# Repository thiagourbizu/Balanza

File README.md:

Balanza para Self-Checkout Girboy

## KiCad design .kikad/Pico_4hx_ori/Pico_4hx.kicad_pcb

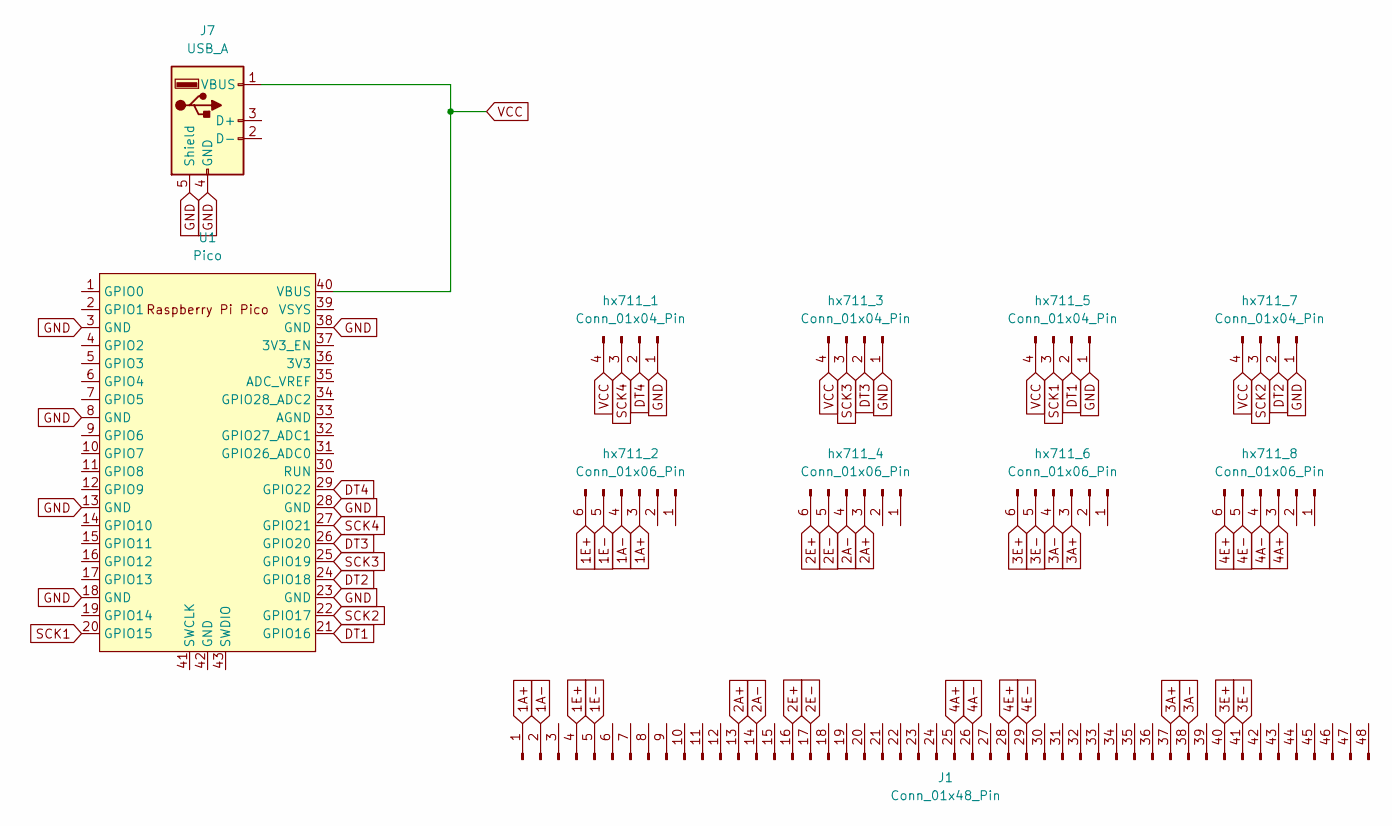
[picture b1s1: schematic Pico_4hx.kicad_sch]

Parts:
J1: Conn_01x48_Pin; RJ45_Amphenol_RJHSE538X-04
J7: USB_A; USB_A_Molex_67643_Horizontal
U1: Pico; RPi_Pico_SMD_TH
hx711_1, hx711_3, hx711_5, hx711_7: Conn_01x04_Pin; PinSocket_1x04_P2.54mm_Vertical
hx711_2, hx711_4, hx711_6, hx711_8: Conn_01x06_Pin; PinSocket_1x06_P2.54mm_Vertical

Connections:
1A+: J1.1, hx711_2.3
1A-: J1.2, hx711_2.4
1E+: J1.4, hx711_2.6
1E-: J1.5, hx711_2.5
2A+: J1.13, hx711_4.3
2A-: J1.14, hx711_4.4
2E+: J1.16, hx711_4.6
2E-: J1.17, hx711_4.5
3A+: J1.37, hx711_6.3
3A-: J1.38, hx711_6.4
3E+: J1.40, hx711_6.6
3E-: J1.41, hx711_6.5
4A+: J1.25, hx711_8.3
4A-: J1.26, hx711_8.4
4E+: J1.28, hx711_8.6
4E-: J1.29, hx711_8.5
DT1: U1.21 (GPIO16), hx711_5.2
DT2: U1.24 (GPIO18), hx711_7.2
DT3: U1.26 (GPIO20), hx711_3.2
DT4: U1.29 (GPIO22), hx711_1.2
GND: J7.4 (GND), J7.5 (Shield), U1.3 (GND), U1.8 (GND), U1.13 (GND), U1.18 (GND), U1.23 (GND), U1.28 (GND), U1.38 (GND), hx711_1.1, hx711_3.1, hx711_5.1, hx711_7.1
SCK1: U1.20 (GPIO15), hx711_5.3
SCK2: U1.22 (GPIO17), hx711_7.3
SCK3: U1.25 (GPIO19), hx711_3.3
SCK4: U1.27 (GPIO21), hx711_1.3
VCC: J7.1 (VBUS), U1.40 (VBUS), hx711_1.4, hx711_3.4, hx711_5.4, hx711_7.4

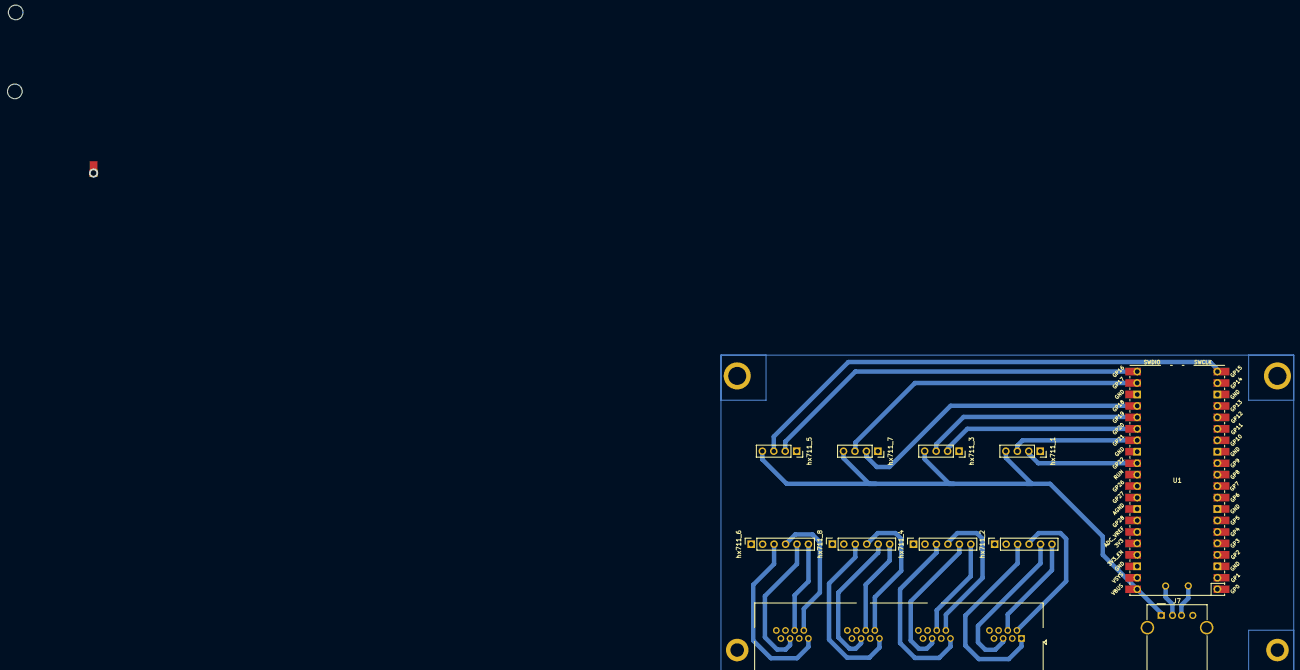
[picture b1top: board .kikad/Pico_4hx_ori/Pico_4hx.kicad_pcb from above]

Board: 2 copper layers, 11 parts (0 on the bottom side), 26 nets.

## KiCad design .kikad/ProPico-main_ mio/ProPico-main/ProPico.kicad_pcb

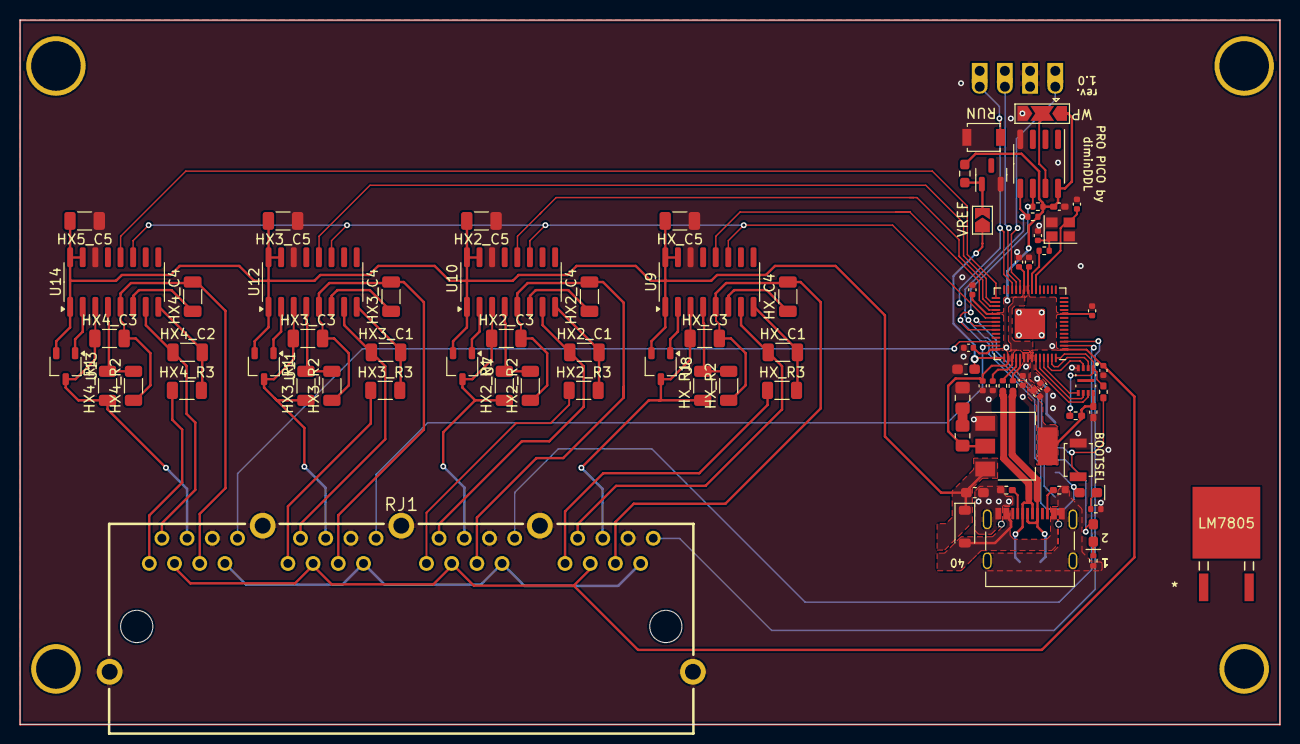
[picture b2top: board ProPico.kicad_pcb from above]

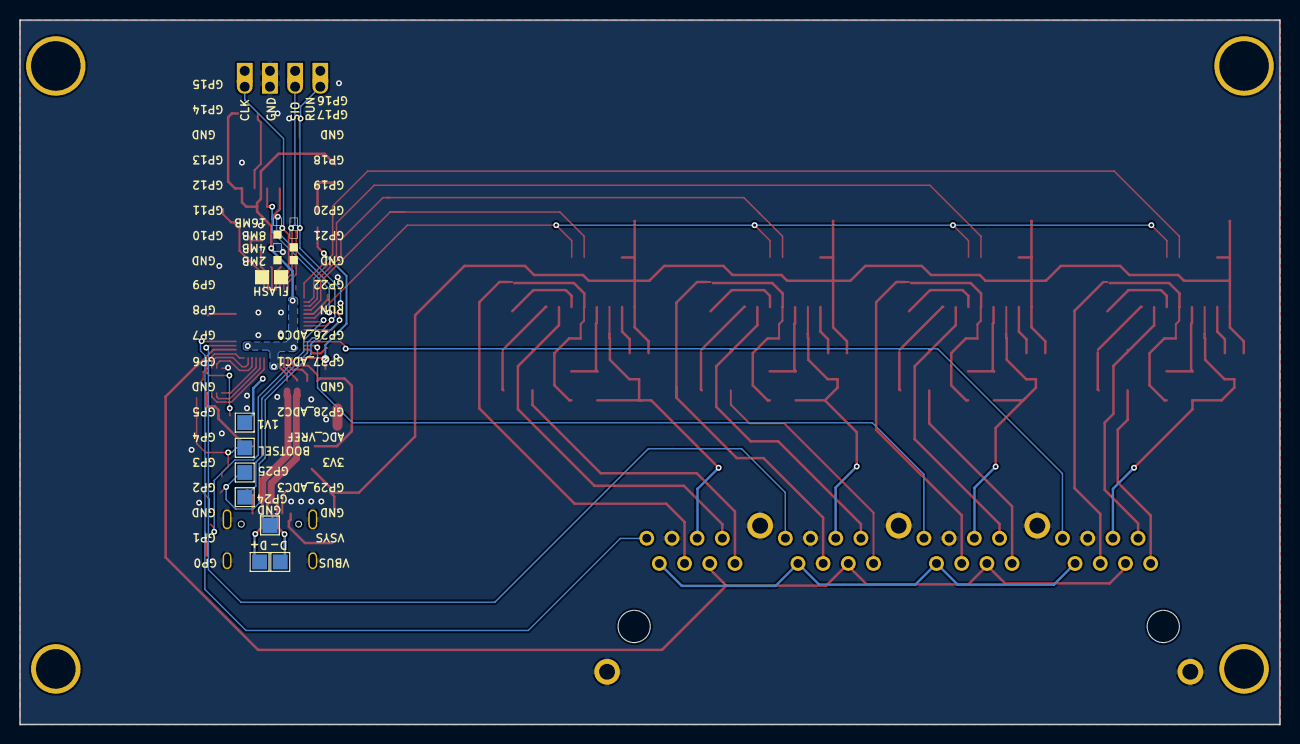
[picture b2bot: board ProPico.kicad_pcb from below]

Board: 2 copper layers, 127.0 x 71.0 mm, 91 parts (7 on the bottom side), 75 nets.

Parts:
C1, C5: 100n; C_0402_1005Metric_Pad0.74x0.62mm_HandSolder
C2, C3: 18p; C_0402_1005Metric
C4: 2.2u; C_0603_1608Metric_Pad1.08x0.95mm_HandSolder
C6: 10u; C_0805_2012Metric_Pad1.18x1.45mm_HandSolder
C7: 10n C0G; C_0603_1608Metric_Pad1.08x0.95mm_HandSolder
C8, C9, C11, C13, C14, C15, C16, C17, C18: 100n; C_0402_1005Metric
C10, C12: 1u; C_0402_1005Metric
D1: B5819W; D_SOD-123
D2, D3: LED; LED_0603_1608Metric_Pad1.05x0.95mm_HandSolder
HX2_C1, HX2_C3, HX3_C1, HX3_C3, HX4_C2, HX4_C3: 0.1uF; C_1206_3216Metric
HX2_C4, HX2_C5, HX3_C4, HX3_C5, HX4_C4, HX5_C5: 10uF; C_1206_3216Metric
HX2_R1, HX3_R1, HX4_R1: 20k; R_1206_3216Metric
HX2_R2, HX3_R2, HX4_R2: 8.2k; R_1206_3216Metric
HX2_R3, HX3_R3, HX4_R3: 1k; R_1206_3216Metric
HX_C1, HX_C3: 0.1uF; C_1206_3216Metric
HX_C4, HX_C5: 10uF; C_1206_3216Metric
HX_R1: 20k; R_1206_3216Metric
HX_R2: 8.2k; R_1206_3216Metric
HX_R3: 1k; R_1206_3216Metric
J1: USB_C_Receptacle_USB2.0; USB_C_Receptacle_Palconn_UTC16-G
J2: SWD; Pico_4pin
JP1: EEPROM_WP; SolderJumper-3_P2.0mm_Open_TrianglePad1.0x1.5mm
JP2: VREF; SolderJumper-2_P1.3mm_Open_TrianglePad1.0x1.5mm
LM7805: MC7805CDTRKG; DPAK-3_ONS-M
R1: 1k; R_0402_1005Metric_Pad0.72x0.64mm_HandSolder
R2: DNP; R_0402_1005Metric_Pad0.72x0.64mm_HandSolder
R3, R4: 5.1k; R_0402_1005Metric_Pad0.72x0.64mm_HandSolder
R5, R10, R11, R12, R13: 1k; R_0402_1005Metric
R6: 470mOhm; R_0805_2012Metric_Pad1.20x1.40mm_HandSolder
R7: 150; R_0603_1608Metric_Pad0.98x0.95mm_HandSolder
R8, R9: 27; R_0402_1005Metric
RJ1: DS1129-02-S80BP
SW1: BOOTSEL; SW_SPST_B3U-1000P
SW2: RES; SW_SPST_B3U-1000P
TP1: BOOTSEL; TestPoint_Pad_1.5x1.5mm
TP2: VREG; TestPoint_Pad_1.5x1.5mm
TP3: GP25; TestPoint_Pad_1.5x1.5mm
TP4: GND; TestPoint_Pad_1.5x1.5mm
TP5: D+; TestPoint_Pad_1.5x1.5mm
TP6: GP24; TestPoint_Pad_1.5x1.5mm
TP7: D-; TestPoint_Pad_1.5x1.5mm
U1: FM24CL16B; SOIC-8_3.9x4.9mm_P1.27mm
U2: W25Q16JVUXIQ; IC_W25Q16JVUXIQ_TR
U3: AMS1117-3.3; SOT-223-3_TabPin2
U4: LM4040DBZ-3; SOT-23
U5: RP2040; RP2040-QFN-56
U7, U8, U11, U13: MMBT5550LT1G; TSOT-23
U9, U10, U12, U14: HX711; SOP-16_3.9x9.9mm_P1.27mm
Y1: ECS-120-12-36-AGN-TR3; Crystal_SMD_2520-4Pin_2.5x2.0mm

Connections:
1A+: HX_R3.1, RJ1.41 (D1)
1A-: HX_C1.1, RJ1.42 (D2), U9.7 (INA-)
1E+: HX_C3.1, HX_R1.1, RJ1.44 (D4), U8.3 (COLLECTOR), U9.3 (AVDD)
1E-: HX_C3.2, HX_C4.2, HX_R2.1, RJ1.45 (D5), U9.5 (AGND)
2A+: HX2_R3.1, RJ1.31 (C1)
2A-: HX2_C1.1, RJ1.32 (C2), U10.7 (INA-)
2E+: HX2_C3.1, HX2_R1.1, RJ1.34 (C4), U7.3 (COLLECTOR), U10.3 (AVDD)
2E-: HX2_C3.2, HX2_C4.2, HX2_R2.1, RJ1.35 (C5), U10.5 (AGND)
3.3V: C1.1, C5.1, C11.1, C12.1, C13.1, C14.1, C15.1, C16.1, C17.1, C18.1, JP1.1 (A), R2.1, R6.2, R7.2, R10.1, R11.1, RJ1.13 (A3), RJ1.23 (B3), RJ1.33 (C3), RJ1.43 (D3), U1.8 (VDD), U2.8 (VCC), U3.2 (VO), U5.1 (IOVDD), U5.10 (IOVDD), U5.22 (IOVDD), U5.33 (IOVDD), U5.42 (IOVDD), U5.44 (VREG_IN), U5.48 (USB_VDD), U5.49 (IOVDD)
3A+: HX3_R3.1, RJ1.21 (B1)
3A-: HX3_C1.1, RJ1.22 (B2), U12.7 (INA-)
3E+: HX3_C3.1, HX3_R1.1, RJ1.24 (B4), U11.3 (COLLECTOR), U12.3 (AVDD)
3E-: HX3_C3.2, HX3_C4.2, HX3_R2.1, RJ1.25 (B5), U12.5 (AGND)
4A+: HX4_R3.1, RJ1.11 (A1)
4A-: HX4_C2.1, RJ1.12 (A2), U14.7 (INA-)
4E+: HX4_C3.1, HX4_R1.1, RJ1.14 (A4), U13.3 (COLLECTOR), U14.3 (AVDD)
4E-: HX4_C3.2, HX4_C4.2, HX4_R2.1, RJ1.15 (A5), U14.5 (AGND)
+1V1: C8.1, C9.1, C10.1, TP2.1, U5.23 (DVDD), U5.45 (VREG_VOUT), U5.50 (DVDD)
/3V0_VREF: JP2.2 (B), R7.1, U4.1 (K)
/ADC_VREF: C7.1, JP2.1 (A), U5.43 (ADC_AVDD)
/D+: J1.A6 (D+), J1.B6 (D+), R8.1, TP5.1
/D-: J1.A7 (D-), J1.B7 (D-), R9.1, TP7.1
/DN: R9.2, U5.46 (USB_DM)
/DP: R8.2, U5.47 (USB_DP)
/EEPROM_SCL: D3.2 (A), R11.2, TP3.1, U1.6 (SCL), U5.37 (GPIO25)
/EEPROM_SDA: R10.2, TP6.1, U1.5 (SDA), U5.36 (GPIO24)
/EEPROM_WP: JP1.2 (C), U1.7 (WP)
/GPIO23: D2.2 (A), U5.35 (GPIO23)
/QSPI_SCLK: U2.6 (CLK), U5.52 (QSPI_SCLK)
/QSPI_SD0: U2.5 (DI(IO0)), U5.53 (QSPI_SD0)
/QSPI_SD1: U2.2 (DO(IO1)), U5.55 (QSPI_SD1)
/QSPI_SD2: U2.3 (IO2), U5.54 (QSPI_SD2)
/QSPI_SD3: U2.7 (IO3), U5.51 (QSPI_SD3)
/QSPI_SS: R1.1, R2.2, U2.1 (~CS), U5.56 (QSPI_SS)
/RUN: J2.4, SW2.1, U5.26 (RUN)
/SWCLK: J2.1, U5.24 (SWCLK)
/SWD: J2.3, U5.25 (SWD)
/XIN: C2.1, U5.20 (XIN), Y1.3
/XOUT: R5.1, U5.21 (XOUT)
DT1: U5.32 (GPIO21), U9.12 (DOUT)
DT2: U5.31 (GPIO20), U10.12 (DOUT)
DT3: U5.30 (GPIO19), U12.12 (DOUT)
DT4: U5.29 (GPIO18), U14.12 (DOUT)
GND: C1.2, C2.2, C3.2, C4.2, C5.2, C6.2, C7.2, C8.2, C9.2, C10.2, C11.2, C12.2, C13.2, C14.2, C15.2, C16.2, C17.2, C18.2, HX2_C5.1, HX3_C5.1, HX5_C5.1, HX_C5.1, J1.A1 (GND), J1.A12 (GND), J1.B1 (GND), J1.B12 (GND), J1.S1 (SHIELD), J2.2, JP1.3 (B), R3.2, R4.2, R12.2, R13.2, RJ1.16 (A6), RJ1.26 (B6), RJ1.36 (C6), RJ1.46 (D6), RJ1.EH, SW1.1, SW2.2, TP4.1, U1.4 (VSS), U2.4 (GND), U3.1 (GND), U4.2 (A), U5.19 (TESTEN), U5.57 (GND), U9.14 (XI), U10.14 (XI), U12.14 (XI), U14.14 (XI), Y1.2, Y1.4
unnamed: C3.1, R5.2, Y1.1
unnamed: C6.1, R6.1
unnamed: D2.1 (K), R12.1
unnamed: D3.1 (K), R13.1
unnamed: J1.A5 (CC1), R4.1
unnamed: J1.B5 (CC2), R3.1
unnamed: R1.2, SW1.2, TP1.1
unnamed: U8.1 (BASE), U9.2 (BASE)
unnamed: HX_C1.2, HX_R3.2, U9.8 (INA+)
unnamed: HX_C4.1, U9.6 (VBG)
unnamed: HX_R1.2, HX_R2.2, U9.4 (VFB)
unnamed: U7.1 (BASE), U10.2 (BASE)
unnamed: HX2_C1.2, HX2_R3.2, U10.8 (INA+)
unnamed: HX2_C4.1, U10.6 (VBG)
unnamed: HX2_R1.2, HX2_R2.2, U10.4 (VFB)
unnamed: U11.1 (BASE), U12.2 (BASE)
unnamed: HX3_C1.2, HX3_R3.2, U12.8 (INA+)
unnamed: HX3_C4.1, U12.6 (VBG)
unnamed: HX3_R1.2, HX3_R2.2, U12.4 (VFB)
unnamed: U13.1 (BASE), U14.2 (BASE)
unnamed: HX4_C2.2, HX4_R3.2, U14.8 (INA+)
unnamed: HX4_C4.1, U14.6 (VBG)
unnamed: HX4_R1.2, HX4_R2.2, U14.4 (VFB)
SCK: U5.34 (GPIO22), U9.11 (PD_SCK), U10.11 (PD_SCK), U12.11 (PD_SCK), U14.11 (PD_SCK)
SCL: RJ1.17 (A7), RJ1.27 (B7), RJ1.37 (C7), RJ1.47 (D7)
SDA1: RJ1.48 (D8), U5.3 (GPIO1)
SDA2: RJ1.38 (C8), U5.2 (GPIO0)
SDA3: RJ1.28 (B8), U5.41 (GPIO29_ADC3)
SDA4: RJ1.18 (A8), U5.40 (GPIO28_ADC2)
VBUS: D1.2 (A), J1.A4 (VBUS), J1.A9 (VBUS), J1.B4 (VBUS), J1.B9 (VBUS)
VCC: C4.1, D1.1 (K), HX2_C5.2, HX3_C5.2, HX5_C5.2, HX_C5.2, U3.3 (VI), U7.2 (EMITTER), U8.2 (EMITTER), U9.1 (VSUP), U9.15 (RATE), U9.16 (DVDD), U10.1 (VSUP), U10.15 (RATE), U10.16 (DVDD), U11.2 (EMITTER), U12.1 (VSUP), U12.15 (RATE), U12.16 (DVDD), U13.2 (EMITTER), U14.1 (VSUP), U14.15 (RATE), U14.16 (DVDD)

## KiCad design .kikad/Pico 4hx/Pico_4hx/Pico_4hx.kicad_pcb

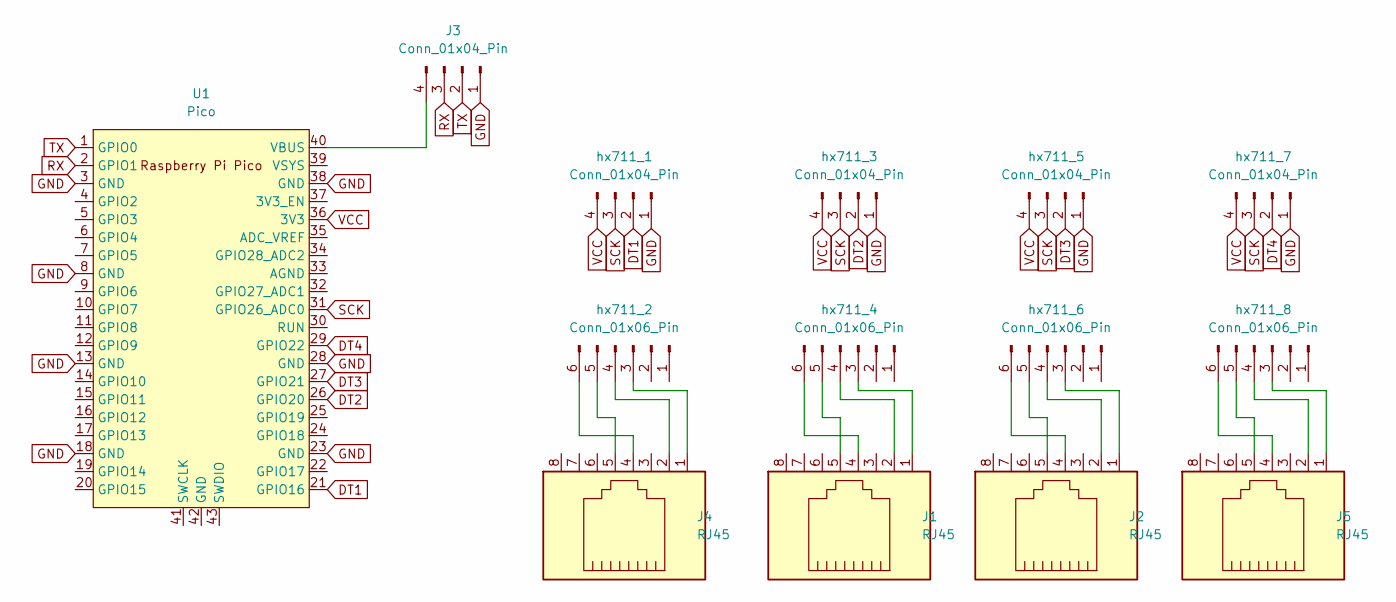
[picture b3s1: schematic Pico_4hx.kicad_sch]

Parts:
J1, J2, J4, J5: RJ45; RJ45_Amphenol_54602-x08_Horizontal
J3: Conn_01x04_Pin; PinSocket_1x04_P2.54mm_Vertical
U1: Pico; RPi_Pico_SMD_TH
hx711_1, hx711_3, hx711_5, hx711_7: Conn_01x04_Pin; PinSocket_1x04_P2.54mm_Vertical
hx711_2, hx711_4, hx711_6, hx711_8: Conn_01x06_Pin; PinSocket_1x06_P2.54mm_Vertical

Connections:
DT1: U1.21 (GPIO16), hx711_1.2
DT2: U1.26 (GPIO20), hx711_3.2
DT3: U1.27 (GPIO21), hx711_5.2
DT4: U1.29 (GPIO22), hx711_7.2
GND: J3.1, U1.3 (GND), U1.8 (GND), U1.13 (GND), U1.18 (GND), U1.23 (GND), U1.28 (GND), U1.38 (GND), hx711_1.1, hx711_3.1, hx711_5.1, hx711_7.1
unnamed: J3.4, U1.40 (VBUS)
unnamed: J4.1, hx711_2.3
unnamed: J4.2, hx711_2.4
unnamed: J4.5, hx711_2.5
unnamed: J4.4, hx711_2.6
unnamed: J1.1, hx711_4.3
unnamed: J1.2, hx711_4.4
unnamed: J1.5, hx711_4.5
unnamed: J1.4, hx711_4.6
unnamed: J2.1, hx711_6.3
unnamed: J2.2, hx711_6.4
unnamed: J2.5, hx711_6.5
unnamed: J2.4, hx711_6.6
unnamed: J5.1, hx711_8.3
unnamed: J5.2, hx711_8.4
unnamed: J5.5, hx711_8.5
unnamed: J5.4, hx711_8.6
RX: J3.3, U1.2 (GPIO1)
SCK: U1.31 (GPIO26_ADC0), hx711_1.3, hx711_3.3, hx711_5.3, hx711_7.3
TX: J3.2, U1.1 (GPIO0)
VCC: U1.36 (3V3), hx711_1.4, hx711_3.4, hx711_5.4, hx711_7.4

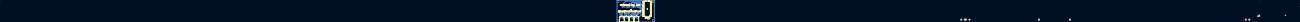
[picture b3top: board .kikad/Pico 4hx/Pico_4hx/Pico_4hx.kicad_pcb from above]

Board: 2 copper layers, 14 parts (0 on the bottom side), 26 nets.

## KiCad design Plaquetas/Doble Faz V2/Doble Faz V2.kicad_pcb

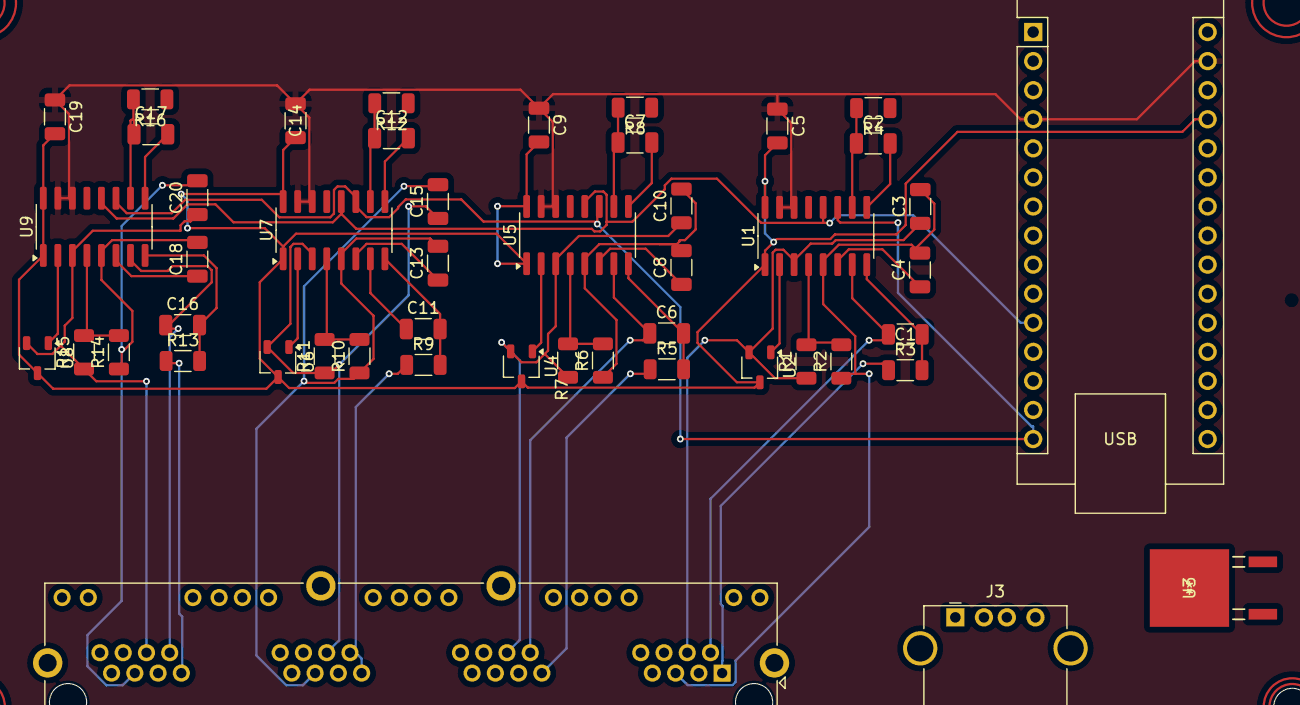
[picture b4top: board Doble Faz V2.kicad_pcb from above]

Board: 2 copper layers, 48 parts (0 on the bottom side), 44 nets.

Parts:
A2: Arduino_Nano_v3.x; Arduino_Nano
C1, C2, C3, C4, C5, C6, C7, C8, C9, C10, C11, C12, C13, C14, C15, C16, C17, C18, C19, C20: C; C_1206_3216Metric
J2: Conn_01x48_Pin; RJ45_Amphenol_RJHSE538X-04
J3: USB_B; USB_A_Stewart_SS-52100-001_Horizontal
R1, R7, R11, R15: R1 20k; R_1206_3216Metric
R2, R6, R10, R14: R2 8.2k; R_1206_3216Metric
R3, R5, R9, R13: R3 1.2k; R_1206_3216Metric
R4, R8, R12, R16: R4 1.2k; R_1206_3216Metric
U1, U5, U7, U9: HX711; SOP-16_3.9x9.9mm_P1.27mm
U2, U4, U6, U8: MMBT5550LT1G; TSOT-23
U3: MC7805CDTRKG; DPAK-3_ONS

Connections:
1A+: J2.1, R3.1
1A-: C1.1, J2.2, U1.7 (INA-)
1B-: C2.2, U1.9 (INB-)
1E+: C3.1, J2.4, R1.1, U1.3 (AVDD), U2.2 (EMITTER)
1E-: C3.2, C4.2, J2.5, R2.1, U1.5 (AGND)
2A+: J2.13, R5.1
2A-: C6.1, J2.14, U5.7 (INA-)
2B-: C7.2, U5.9 (INB-)
2E+: C10.1, J2.16, R7.1, U4.2 (EMITTER), U5.3 (AVDD)
3A+: J2.25, J2.26, R9.1
3A-: C11.1, U7.7 (INA-)
3B-: C12.2, U7.9 (INB-)
3E+: C15.1, J2.28, R11.1, U6.2 (EMITTER), U7.3 (AVDD)
3E-: C13.2, C15.2, J2.29, R10.1, U7.5 (AGND)
4A+: J2.37, R13.1
4A-: C16.1, J2.38, U9.7 (INA-)
4B-: C17.2, U9.9 (INB-)
4E+: C20.1, J2.40, R15.1, U8.2 (EMITTER), U9.3 (AVDD)
4E-: C18.2, C20.2, J2.41, R14.1, U9.5 (AGND)
DT1: A2.11 (D8), U1.12 (DOUT), U5.12 (DOUT), U7.12 (DOUT), U9.12 (DOUT)
GND: A2.4 (GND), A2.29 (GND), C5.1, C9.1, C14.1, C19.1, U1.14 (XI), U1.15 (RATE), U5.14 (XI), U5.15 (RATE), U7.14 (XI), U7.15 (RATE), U9.14 (XI), U9.15 (RATE)
unnamed: U1.2 (BASE), U2.1 (BASE)
unnamed: C1.2, R3.2, U1.8 (INA+)
unnamed: C2.1, R4.2, U1.10 (INB+)
unnamed: C4.1, U1.6 (VBG)
unnamed: R1.2, R2.2, U1.4 (VFB)
unnamed: U4.1 (BASE), U5.2 (BASE)
unnamed: C8.2, C10.2, R6.1, U5.5 (AGND)
unnamed: C6.2, R5.2, U5.8 (INA+)
unnamed: C7.1, R8.2, U5.10 (INB+)
unnamed: C8.1, U5.6 (VBG)
unnamed: R6.2, R7.2, U5.4 (VFB)
unnamed: U6.1 (BASE), U7.2 (BASE)
unnamed: C11.2, R9.2, U7.8 (INA+)
unnamed: C12.1, R12.2, U7.10 (INB+)
unnamed: C13.1, U7.6 (VBG)
unnamed: R10.2, R11.2, U7.4 (VFB)
unnamed: U8.1 (BASE), U9.2 (BASE)
unnamed: C16.2, R13.2, U9.8 (INA+)
unnamed: C17.1, R16.2, U9.10 (INB+)
unnamed: C18.1, U9.6 (VBG)
unnamed: R14.2, R15.2, U9.4 (VFB)
SCK: A2.15 (D12), U1.11 (PD_SCK), U5.11 (PD_SCK), U7.11 (PD_SCK), U9.11 (PD_SCK)
VCC: A2.27 (+5V), C5.2, C9.2, C14.2, C19.2, U1.1 (VSUP), U1.16 (DVDD), U2.3 (COLLECTOR), U4.3 (COLLECTOR), U5.1 (VSUP), U5.16 (DVDD), U6.3 (COLLECTOR), U7.1 (VSUP), U7.16 (DVDD), U8.3 (COLLECTOR), U9.1 (VSUP), U9.16 (DVDD)

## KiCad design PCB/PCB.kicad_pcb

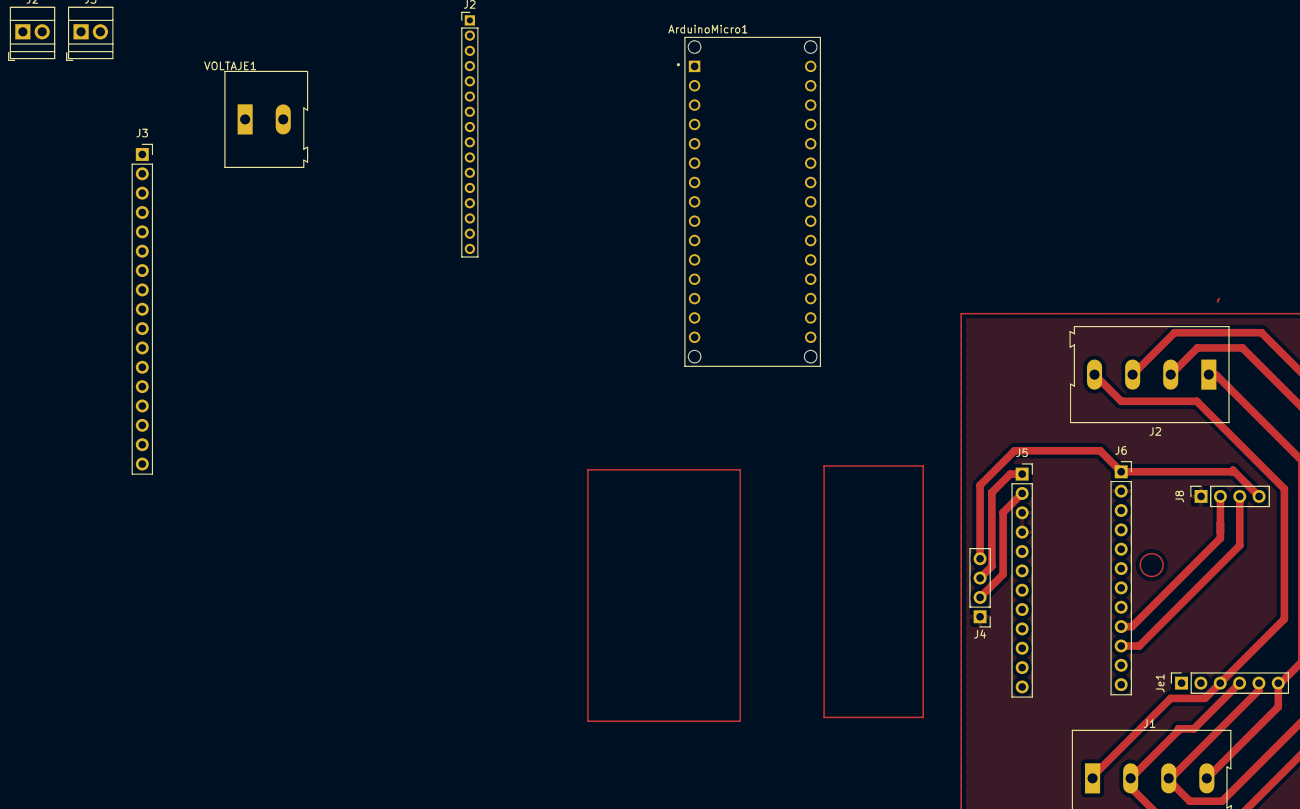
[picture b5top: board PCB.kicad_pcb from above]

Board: 2 copper layers, 13 parts (0 on the bottom side), 10 nets.

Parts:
ArduinoMicro1: A000005; MODULE_A000005
J1, J2#3: Screw_Terminal_01x04; TerminalBlock_Altech_AK300-4_P5.00mm
J2, J3#2: Screw_Terminal_01x02; TerminalBlock_Xinya_XY308-2.54-2P_1x02_P2.54mm_Horizontal
J2#2: Conn_01x16_Socket; PinHeader_1x16_P2.00mm_Vertical
J3: Conn_01x17_Pin; PinSocket_1x17_P2.54mm_Vertical
J4: Conn_01x04_Pin; PinHeader_1x04_P2.54mm_Vertical
J5, J6: Conn_01x12_Pin; PinSocket_1x12_P2.54mm_Vertical
J8: Conn_01x04_Pin; PinSocket_1x04_P2.54mm_Vertical
Je1: Conn_01x06_Pin; PinSocket_1x06_P2.54mm_Vertical
VOLTAJE1: Screw_Terminal_01x02; TerminalBlock_Altech_AK300-2_P5.00mm

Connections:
GND: J4.1, J5.3, J5.4, J6.2, J8.1
unnamed: J1.1, J2#3.4, Je1.3
unnamed: J1.2, J2#3.3, Je1.4
unnamed: J1.3, J2#3.2, Je1.5
unnamed: J1.4, J2#3.1, Je1.6
unnamed: J4.2, J5.2
unnamed: J4.3, J5.1
unnamed: J4.4, J6.1, J8.4
unnamed: J6.9, J8.2
unnamed: J6.10, J8.3

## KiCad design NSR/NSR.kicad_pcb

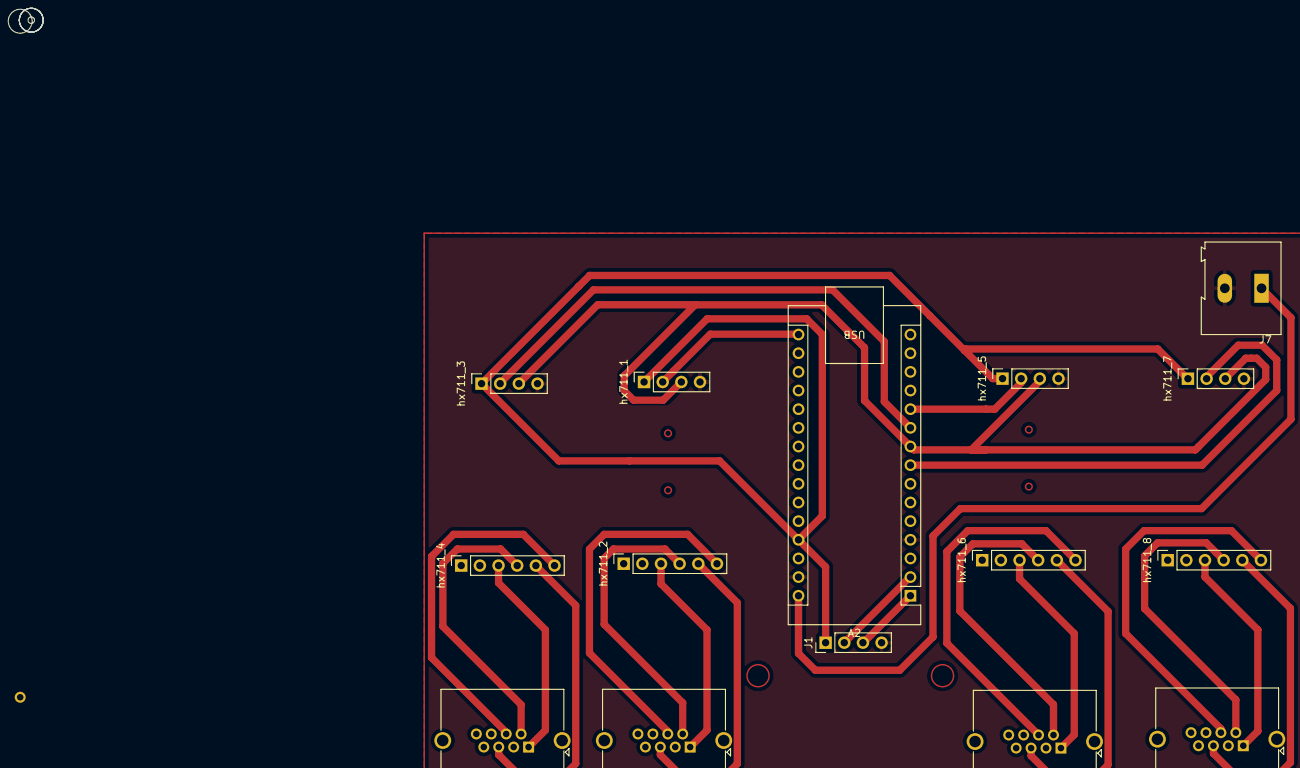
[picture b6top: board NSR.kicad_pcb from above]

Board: 2 copper layers, 15 parts (0 on the bottom side), 26 nets.

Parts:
A2: Arduino_Nano_v3.x; Arduino_Nano
J1: Conn_01x04_Pin; PinHeader_1x04_P2.54mm_Vertical
J2, J3, J4, J5: RJ45; RJ45_Amphenol_RJHSE538X
J7: Screw_Terminal_01x02; TerminalBlock_Altech_AK300-2_P5.00mm
hx711_1, hx711_3, hx711_5, hx711_7: Conn_01x04_Pin; PinSocket_1x04_P2.54mm_Vertical
hx711_2, hx711_4, hx711_6, hx711_8: Conn_01x06_Pin; PinSocket_1x06_P2.54mm_Vertical

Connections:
5V: A2.27 (+5V), J1.1, hx711_1.1, hx711_3.1, hx711_5.1, hx711_7.1
DT1: A2.16 (D13), hx711_1.2
DT2: A2.10 (D7), hx711_3.2
DT3: A2.11 (D8), hx711_5.2
DT4: A2.8 (D5), hx711_7.2
GND: A2.4 (GND), A2.29 (GND), J1.4, J7.2, hx711_1.4, hx711_3.4, hx711_5.4, hx711_7.4
unnamed: J2.1, hx711_2.3
unnamed: J2.2, hx711_2.4
unnamed: J2.5, hx711_2.5
unnamed: J2.4, hx711_2.6
unnamed: J3.1, hx711_4.3
unnamed: J3.2, hx711_4.4
unnamed: J3.5, hx711_4.5
unnamed: J3.4, hx711_4.6
unnamed: J4.1, hx711_6.3
unnamed: J4.2, hx711_6.4
unnamed: J4.5, hx711_6.5
unnamed: J4.4, hx711_6.6
unnamed: J5.1, hx711_8.3
unnamed: J5.2, hx711_8.4
unnamed: J5.5, hx711_8.5
unnamed: J5.4, hx711_8.6
RX: A2.2 (D0/RX), J1.2
SCK: A2.9 (D6), hx711_1.3, hx711_3.3, hx711_5.3, hx711_7.3
TX: A2.1 (D1/TX), J1.3
VIN: A2.30 (VIN), J7.1

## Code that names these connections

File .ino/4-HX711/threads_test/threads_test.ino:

#include "HX711.h"
#include "pico/multicore.h"

// Pines
#define DT1 16
#define SCK1 10

#define DT2 19
#define SCK2 17

#define DT3 20
#define SCK3 18

#define DT4 22
#define SCK4 26

#define N 20
#define THRESHOLD_GRAMS 4.0

HX711 hx1, hx2, hx3, hx4;

volatile float lecturaCore0 = 0;
volatile float lecturaCore1 = 0;
float offset = 0;

// Activación individual
bool active1 = true;
bool active2 = true;
bool active3 = true;
bool active4 = false;

// Factores de calibración
float factor[4] = {126.658, 125.083, 124.173, 125.0}; //A B C D

void setup() {
  Serial.begin(115200);

  hx1.begin(DT1, SCK1); hx1.set_scale(factor[0]); 
  hx2.begin(DT2, SCK2); hx2.set_scale(factor[1]);
  hx3.begin(DT3, SCK3); hx3.set_scale(factor[2]);
  hx4.begin(DT4, SCK4); hx4.set_scale(factor[3]);

  tareGeneral();
  multicore_launch_core1(readCore1);
}

void loop() {

  float total = 0;
  for (int i = 0; i < N; i++) {
    total += hx1.get_units(1);
    total += hx2.get_units(1);
    }
  float avg = total / (N * 3.0);
  avg -= offset;
  if (avg < THRESHOLD_GRAMS && avg > -THRESHOLD_GRAMS) avg = 0.0;
  lecturaCore0 = avg;

  float totalPeso = (lecturaCore0 + lecturaCore1) /1000.0;
  
  Serial.print(totalPeso, 3);
  Serial.print(" kg - ");
  Serial.print(active1);
  Serial.print(active2);
  Serial.print(active3);
  Serial.println(active4);
  
  if (Serial.available()) {
    char comando = Serial.read();

    switch (comando) {
      case 'Z':
        tareGeneral();
      case 'z':
        tareGeneral();
        break;
        
      case '1':
        active1 = !active1;
        Serial.print("CELDA 1 ");
        Serial.println(active1);
        break;

      case '2':
        active2 = !active2;
        Serial.print("CELDA 2 ");
        Serial.println(active2);
        break;

      case '3':
        active3 = !active3;
        Serial.print("CELDA 3 ");
        Serial.println(active3);
        break;

      case '4':
        active4 = !active4;
        Serial.print("CELDA 4 ");
        Serial.println(active4);
        break;
    }
  }
}

// CORE 1
void readCore1() {
    const int samples = N;
    while(true){
      float total = 0;
      for (int i = 0; i < samples; i++) {
          total += hx3.get_units(1);
          total += hx4.get_units(1);
          //delay(5);
      }
      float avg = total / (samples * 3.0);
      avg -= offset;
      if (avg < THRESHOLD_GRAMS && avg > -THRESHOLD_GRAMS) avg = 0.0;
      lecturaCore1 = avg;
    }
}

void tareGeneral() {
  if (active1) hx1.tare();
  if (active2) hx2.tare();
  if (active3) hx3.tare();
  if (active4) hx4.tare();
  Serial.println("Tare general realizado.");
}

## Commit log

2025-01-06 Hola!
2025-01-06 chau
2025-01-13 holas!!
2025-01-13 Cambios 13-01
2025-01-17 17/01
2025-01-20 Lunes 20/01
2025-01-28 28 del 1
2025-03-11 ultimos changes
2025-03-14 avances nueva placa y orden
2025-03-21 nsr pcb
2025-03-27 Adds
2025-03-31 BACK
2025-04-16 16-04
2025-04-16 segunda prueba wallmart
2025-04-23 Limpieza y orden + pico v4
2025-05-05 final antes de prueba
2025-05-06 Despues de Wallmart
2025-05-07 eprom is going
2025-05-07 eprom is going on
2025-05-13 Cambios placa y codigos
2025-05-28 Placa avanzada
2025-06-09 Control
2025-06-13 test sanjusto
2025-06-23 Codigo y placa
2025-06-27 data
2025-07-02 Before Chango
2025-07-03 despues de que ande todo jaja
2025-07-03 Placa
2025-07-11 Codigo final y placa China
